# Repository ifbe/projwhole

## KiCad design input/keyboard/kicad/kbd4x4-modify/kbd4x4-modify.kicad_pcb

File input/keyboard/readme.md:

# ESP32-S3 三模键盘

ESP32-S3 机械键盘：**USB HID / 蓝牙 BLE / WiFi(UDP)** 三路同时输出，每键 WS2812B 灯效，
8×18 与 4×4(arrow) 两种矩阵在编译期切换，板载网页可以改键值、改灯效、看日志、重启/进下载模式。

## 目录

| 路径 | 内容 |
|---|---|
| `code/keyled/` | Arduino 固件（`keyled.ino` + 各模块） |
| `kicad/` | PCB 工程（kbd2x2 / kbd4x4 / kbd5x5 / esp32s3-wroom1 底板） |
| `scad/` | 外壳与键帽（OpenSCAD，以及导出的 stl / 3mf） |

## 其他文档

- [`arduino.md`](arduino.md) —— 开发环境、编译参数、烧录方式、网页入口
- [`gotcha.md`](gotcha.md) —— 踩过的坑（NimBLE / USB CDC / 下载模式 / EEPROM / 中断…）
- [`esp32s3.md`](esp32s3.md) —— ESP32-S3 引脚用途（8x18 + board v2），含未使用脚清单
- [`todo.md`](todo.md) —— 待办与已知问题

## 相关链接

- Arduino ESP32 core：<https://github.com/espressif/arduino-esp32>
- ESP32-S3 产品页/文档：<https://www.espressif.com/en/products/socs/esp32-s3>
- ESP32-BLE-Keyboard：<https://github.com/T-vK/ESP32-BLE-Keyboard>
- Adafruit NeoPixel：<https://github.com/adafruit/Adafruit_NeoPixel>
- esptool：<https://github.com/espressif/esptool>

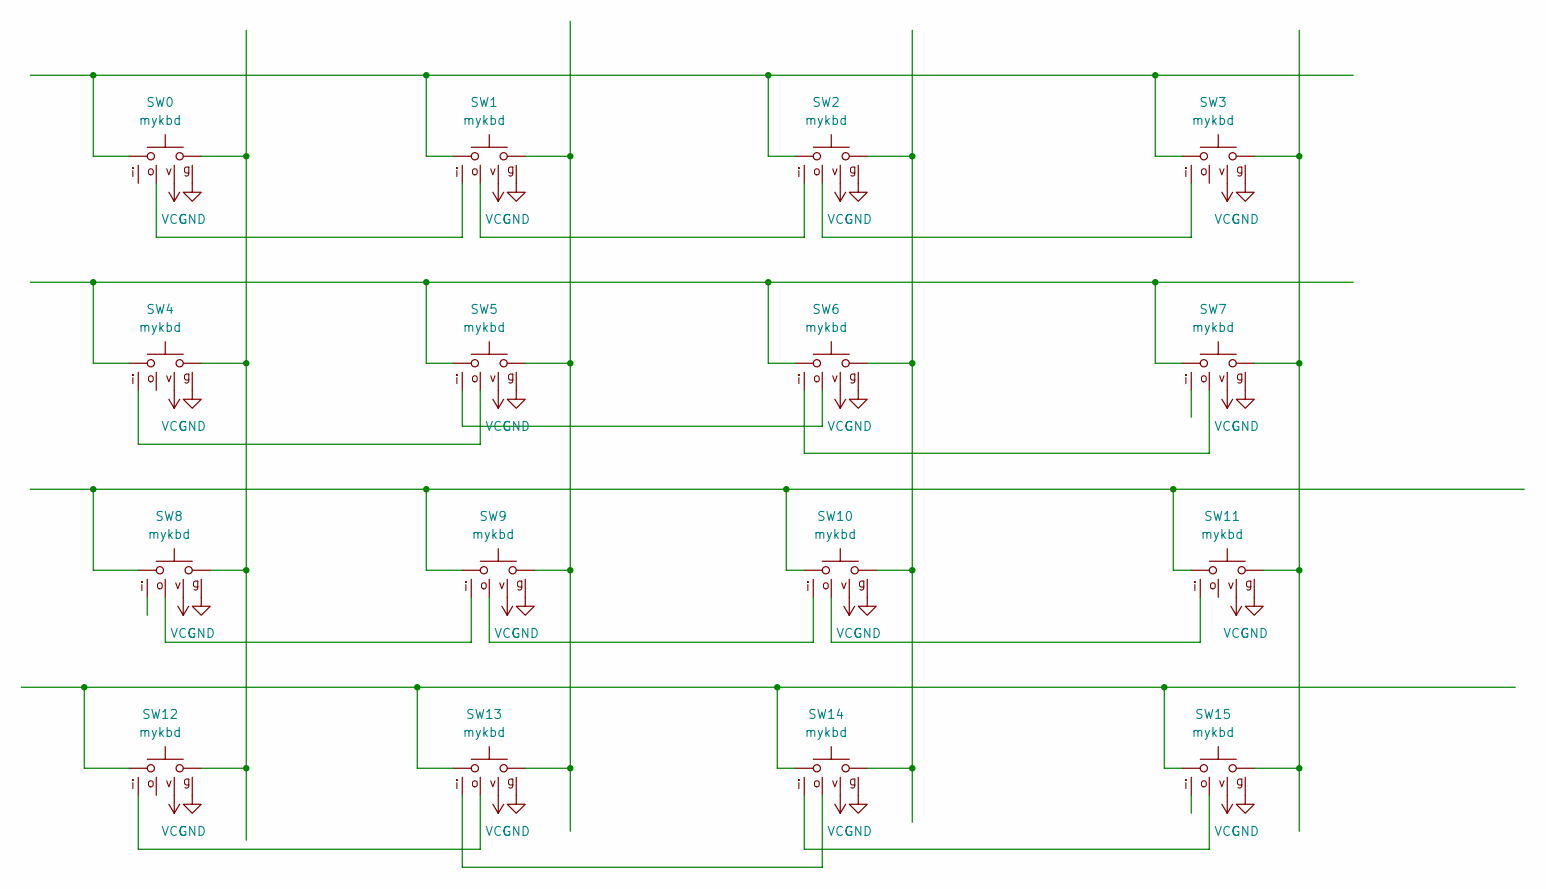
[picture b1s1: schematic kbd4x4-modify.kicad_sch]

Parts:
SW0, SW1, SW2, SW3, SW8, SW9, SW10, SW11: mykbd; seat_ltor
SW4, SW5, SW6, SW7, SW12, SW13, SW14, SW15: mykbd; seat_rtol

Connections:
GND: SW0.6, SW1.6, SW2.6, SW3.6, SW4.6, SW5.6, SW6.6, SW7.6, SW8.6, SW9.6, SW10.6, SW11.6, SW12.6, SW13.6, SW14.6, SW15.6
unnamed: SW0.1, SW1.1, SW2.1, SW3.1
unnamed: SW0.2, SW4.2, SW8.2, SW12.2
unnamed: SW0.4, SW1.3
unnamed: SW1.2, SW5.2, SW9.2, SW13.2
unnamed: SW1.4, SW2.3
unnamed: SW2.4, SW3.3
unnamed: SW4.1, SW5.1, SW6.1, SW7.1
unnamed: SW4.3, SW5.4
unnamed: SW5.3, SW6.4
unnamed: SW6.3, SW7.4
unnamed: SW8.4, SW9.3
unnamed: SW8.1, SW9.1, SW10.1, SW11.1
unnamed: SW2.2, SW6.2, SW10.2, SW14.2
unnamed: SW9.4, SW10.3
unnamed: SW10.4, SW11.3
unnamed: SW3.2, SW7.2, SW11.2, SW15.2
unnamed: SW12.1, SW13.1, SW14.1, SW15.1
unnamed: SW12.3, SW13.4
unnamed: SW13.3, SW14.4
unnamed: SW14.3, SW15.4
VCC: SW0.5, SW1.5, SW2.5, SW3.5, SW4.5, SW5.5, SW6.5, SW7.5, SW8.5, SW9.5, SW10.5, SW11.5, SW12.5, SW13.5, SW14.5, SW15.5

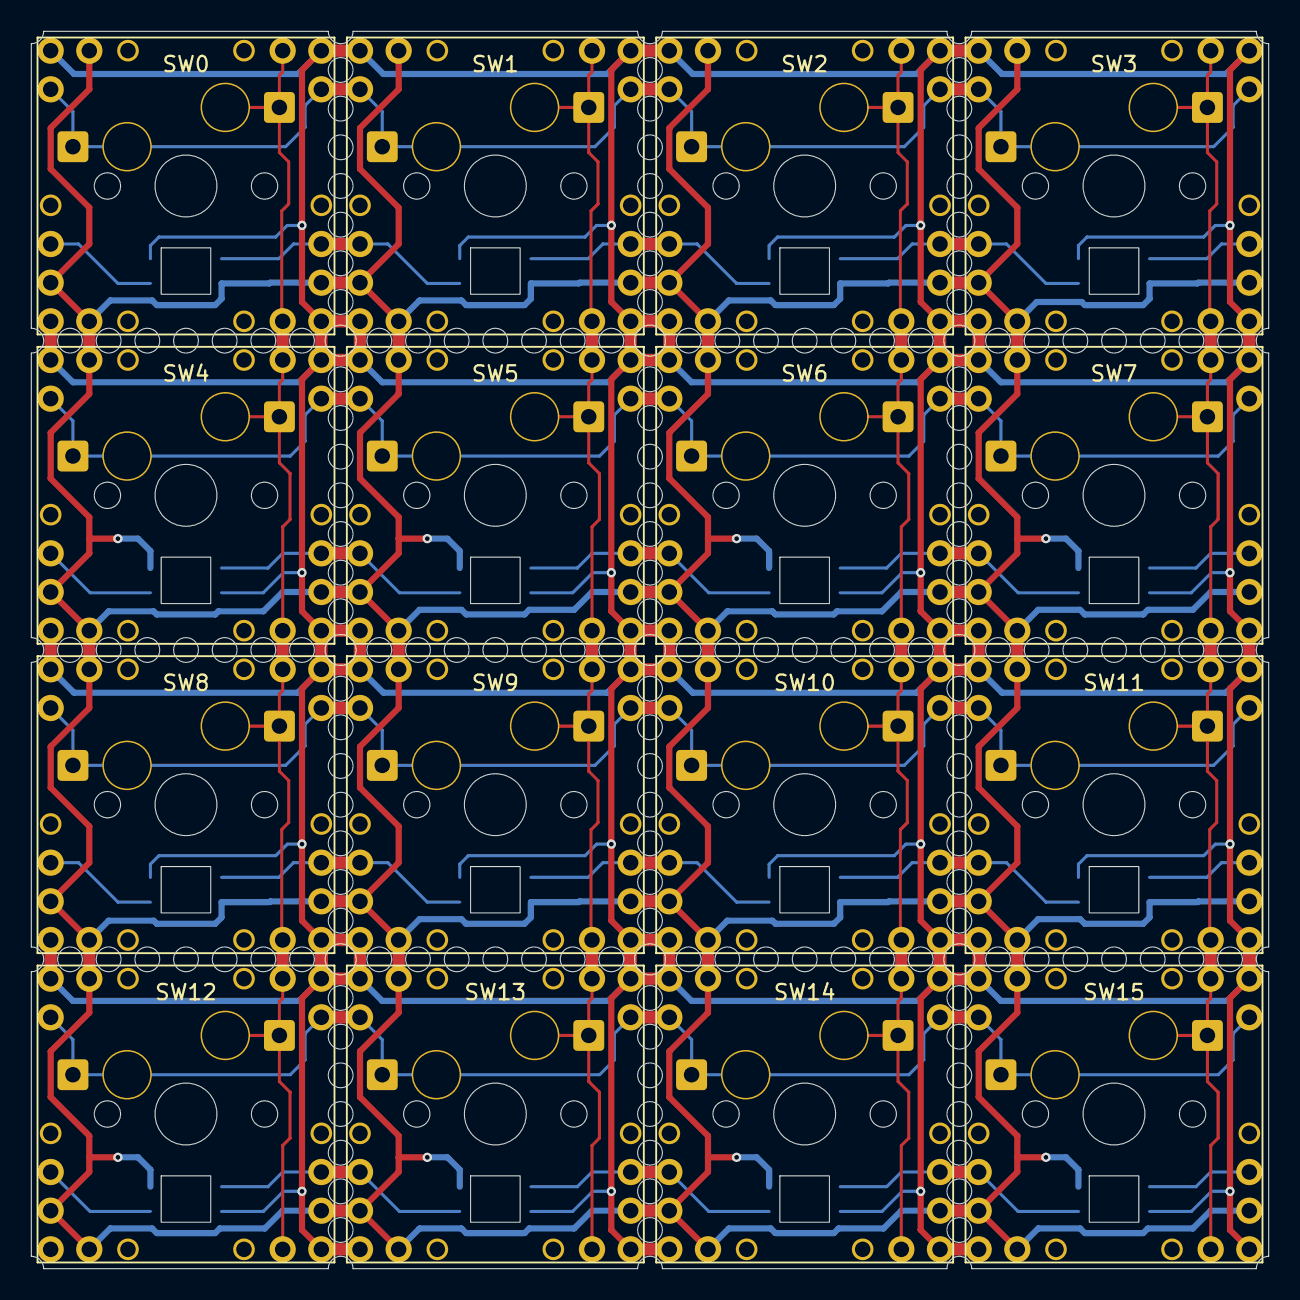
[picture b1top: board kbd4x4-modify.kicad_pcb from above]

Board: 2 copper layers, 80.0 x 80.0 mm, 16 parts (0 on the bottom side), 22 nets.

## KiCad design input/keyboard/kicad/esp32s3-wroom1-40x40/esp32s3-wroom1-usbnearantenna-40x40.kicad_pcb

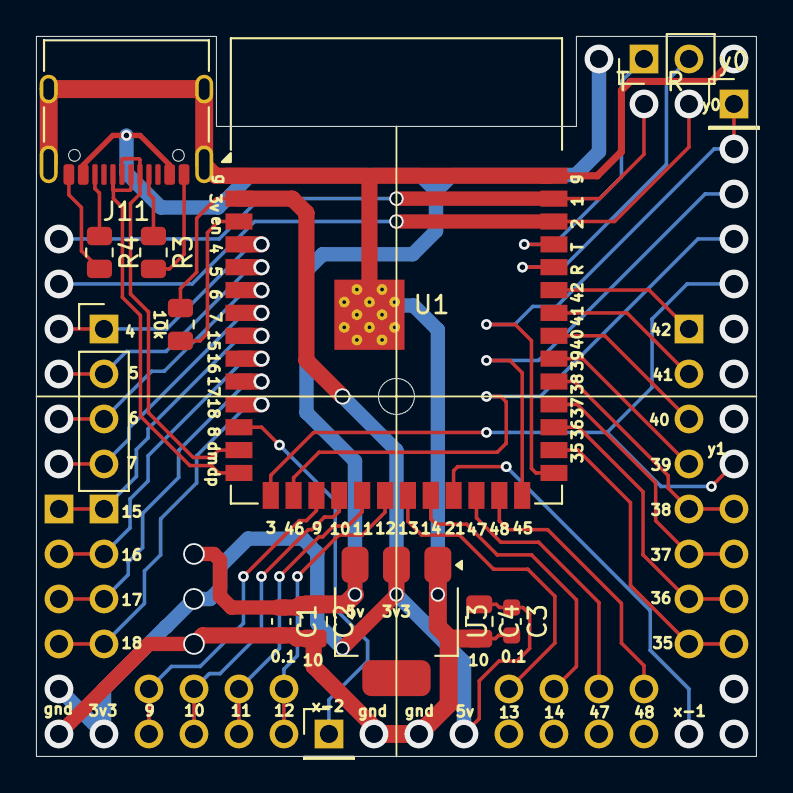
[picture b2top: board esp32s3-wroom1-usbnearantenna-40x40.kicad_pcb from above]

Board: 2 copper layers, 40.0 x 40.0 mm, 14 parts (0 on the bottom side), 16 nets.

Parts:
C1, C3: 0.1uf; C_0603_1608Metric
C2, C4: 10uf; C_0805_2012Metric
J10: Conn_01x01_Pin; PinHeader_1x01_P2.54mm_Vertical
J11: USB_C_Receptacle_USB2.0_16P; USB_C_Receptacle_XKB_U262-16XN-4BVC11
J12: Conn_01x02_Pin; PinHeader_1x02_P2.54mm_Vertical
J14: Conn_01x04_Pin; PinHeader_1x04_P2.54mm_Vertical
R1: R; R_0805_2012Metric
R3, R4: 5.1k; R_0805_2012Metric
U1: ESP32-S3-WROOM-1
U3: TLV1117-33; SOT-223
y0: Conn_01x01_Pin; PinHeader_1x01_P2.54mm_Vertical

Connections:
+3V3: C3.1, C4.1, R1.1, U1.2 (3V3), U3.2 (VO)
+5V: C1.1, C2.1, J11.A4 (VBUS), J11.A9 (VBUS), J11.B4 (VBUS), J11.B9 (VBUS), U3.3 (VI)
GND: C1.2, C2.2, C3.2, C4.2, J11.A1 (GND), J11.A12 (GND), J11.B1 (GND), J11.B12 (GND), J11.SH (SHIELD), R3.2, R4.2, U1.1 (GND), U1.40 (GND), U1.41 (GND), U3.1 (GND)
unnamed: J11.A5 (CC1), R3.1
unnamed: J11.B5 (CC2), R4.1
unnamed: R1.2, U1.3 (EN)
d+: J11.A6 (D+), J11.B6 (D+), U1.14 (USB_D+)
d-: J11.A7 (D-), J11.B7 (D-), U1.13 (USB_D-)
g0: U1.27 (IO0), y0.1
g4: J14.1, U1.4 (IO4)
g5: J14.2, U1.5 (IO5)
g6: J14.3, U1.6 (IO6)
g7: J14.4, U1.7 (IO7)
rx: J12.2, U1.36 (RXD0)
tx: J12.1, U1.37 (TXD0)
xl2: J10.1, U1.12 (IO8)

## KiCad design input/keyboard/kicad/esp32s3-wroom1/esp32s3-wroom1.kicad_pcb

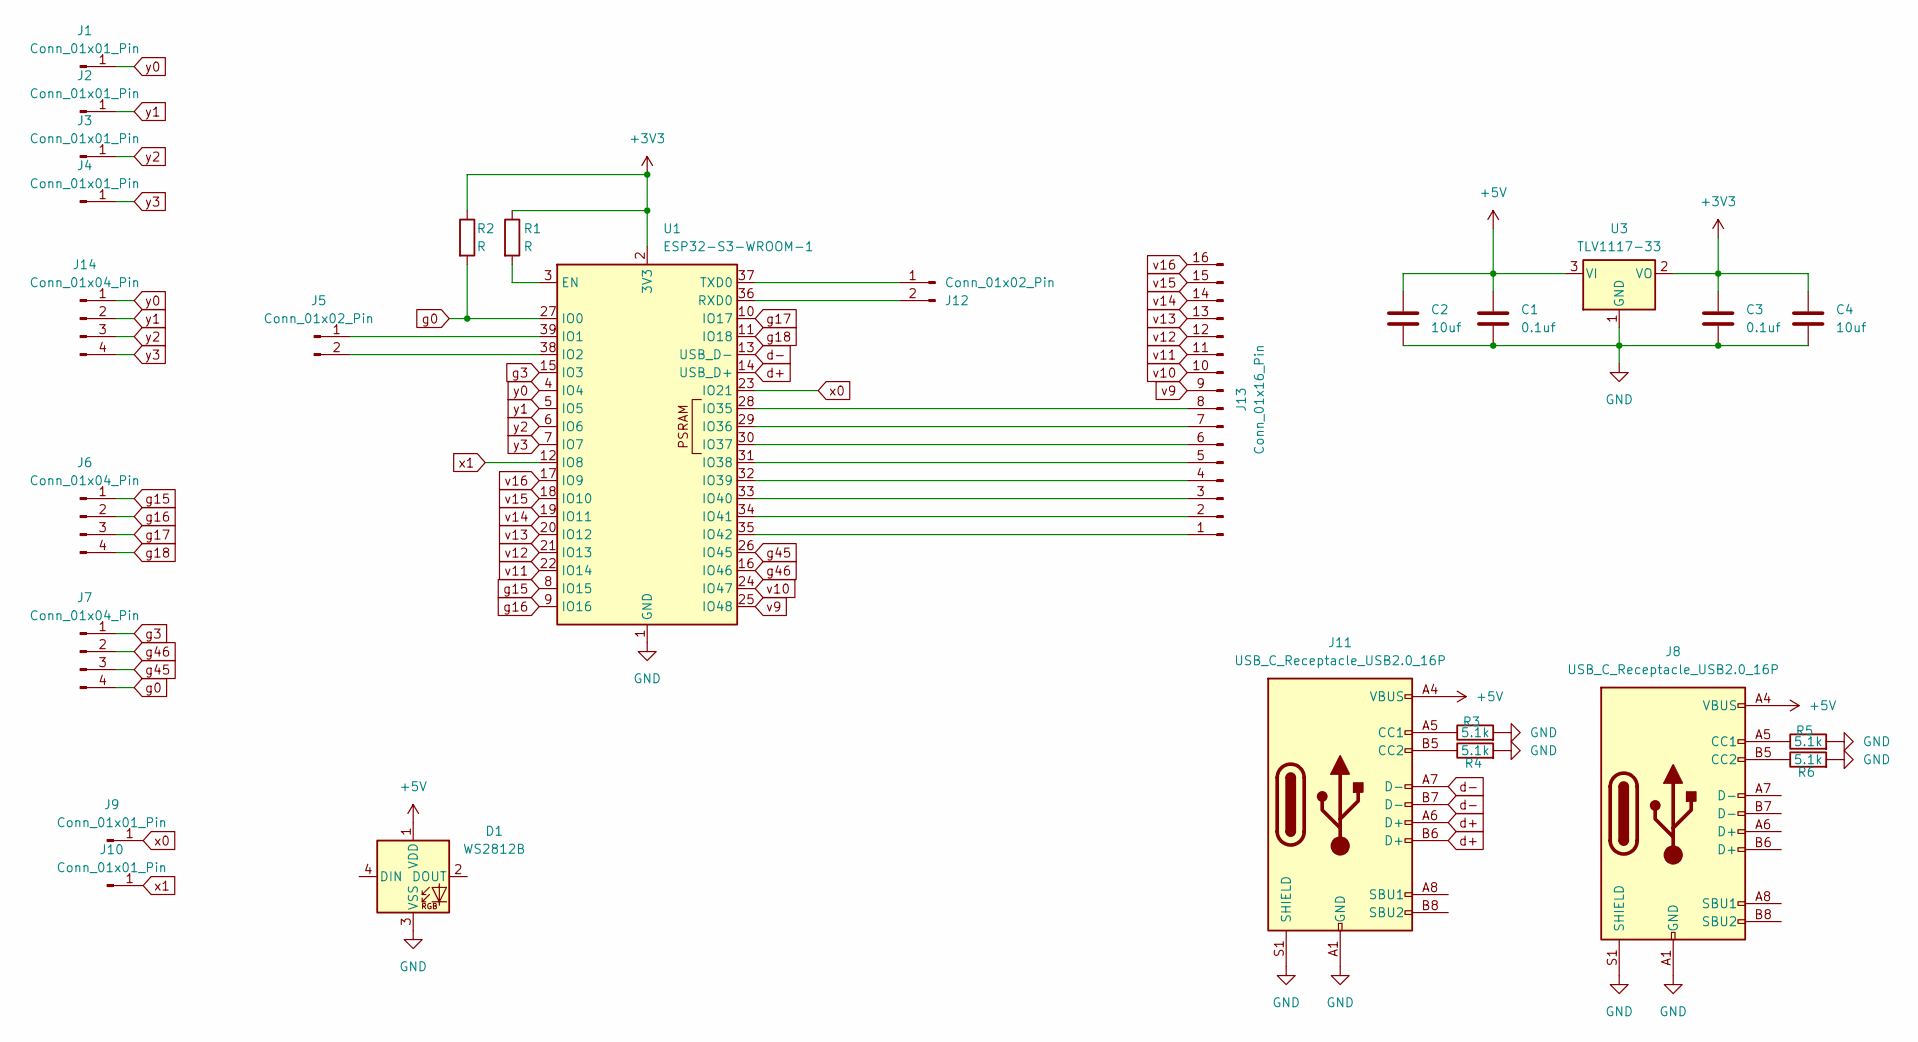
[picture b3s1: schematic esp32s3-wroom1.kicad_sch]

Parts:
C1, C3: 0.1uf; C_0603_1608Metric
C2, C4: 10uf; C_0805_2012Metric
D1: WS2812B; ws2812_3228back
J1, J2, J3, J4, J9, J10: Conn_01x01_Pin; PinHeader_1x01_P2.54mm_Vertical
J5, J12: Conn_01x02_Pin; PinHeader_1x02_P2.54mm_Vertical
J6, J7, J14: Conn_01x04_Pin; PinHeader_1x04_P2.54mm_Vertical
J8, J11: USB_C_Receptacle_USB2.0_16P; USB_C_Receptacle_XKB_U262-16XN-4BVC11
J13: Conn_01x16_Pin; PinHeader_1x16_P2.54mm_Vertical
R1, R2: R; R_0805_2012Metric
R3, R4, R5, R6: 5.1k; R_0805_2012Metric
U1: ESP32-S3-WROOM-1
U3: TLV1117-33; SOT-223

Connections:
+3V3: C3.1, C4.1, R1.1, R2.1, U1.2 (3V3), U3.2 (VO)
+5V: C1.1, C2.1, D1.1 (VDD), J8.A4 (VBUS), J8.A9 (VBUS), J8.B4 (VBUS), J8.B9 (VBUS), J11.A4 (VBUS), J11.A9 (VBUS), J11.B4 (VBUS), J11.B9 (VBUS), U3.3 (VI)
GND: C1.2, C2.2, C3.2, C4.2, D1.3 (VSS), J8.A1 (GND), J8.A12 (GND), J8.B1 (GND), J8.B12 (GND), J8.S1 (SHIELD), J11.A1 (GND), J11.A12 (GND), J11.B1 (GND), J11.B12 (GND), J11.S1 (SHIELD), R3.2, R4.2, R5.2, R6.2, U1.1 (GND), U1.40 (GND), U1.41 (GND), U3.1 (GND)
unnamed: J5.1, U1.39 (IO1)
unnamed: J5.2, U1.38 (IO2)
unnamed: J8.A5 (CC1), R5.1
unnamed: J8.B5 (CC2), R6.1
unnamed: J11.A5 (CC1), R3.1
unnamed: J11.B5 (CC2), R4.1
unnamed: J12.1, U1.37 (TXD0)
unnamed: J12.2, U1.36 (RXD0)
unnamed: J13.1, U1.35 (IO42)
unnamed: J13.2, U1.34 (IO41)
unnamed: J13.3, U1.33 (IO40)
unnamed: J13.4, U1.32 (IO39)
unnamed: J13.5, U1.31 (IO38)
unnamed: J13.6, U1.30 (IO37)
unnamed: J13.7, U1.29 (IO36)
unnamed: J13.8, U1.28 (IO35)
unnamed: R1.2, U1.3 (EN)
d+: J11.A6 (D+), J11.B6 (D+), U1.14 (USB_D+)
d-: J11.A7 (D-), J11.B7 (D-), U1.13 (USB_D-)
g0: J7.4, R2.2, U1.27 (IO0)
g3: J7.1, U1.15 (IO3)
g15: J6.1, U1.8 (IO15)
g16: J6.2, U1.9 (IO16)
g17: J6.3, U1.10 (IO17)
g18: J6.4, U1.11 (IO18)
g45: J7.3, U1.26 (IO45)
g46: J7.2, U1.16 (IO46)
v9: J13.9, U1.25 (IO48)
v10: J13.10, U1.24 (IO47)
v11: J13.11, U1.22 (IO14)
v12: J13.12, U1.21 (IO13)
v13: J13.13, U1.20 (IO12)
v14: J13.14, U1.19 (IO11)
v15: J13.15, U1.18 (IO10)
v16: J13.16, U1.17 (IO9)
x0: J9.1, U1.23 (IO21); also elsewhere on the board
x1: J10.1, U1.12 (IO8)
y0: J1.1, J14.1, U1.4 (IO4)
y1: J2.1, J14.2, U1.5 (IO5)
y2: J3.1, J14.3, U1.6 (IO6)
y3: J4.1, J14.4, U1.7 (IO7)

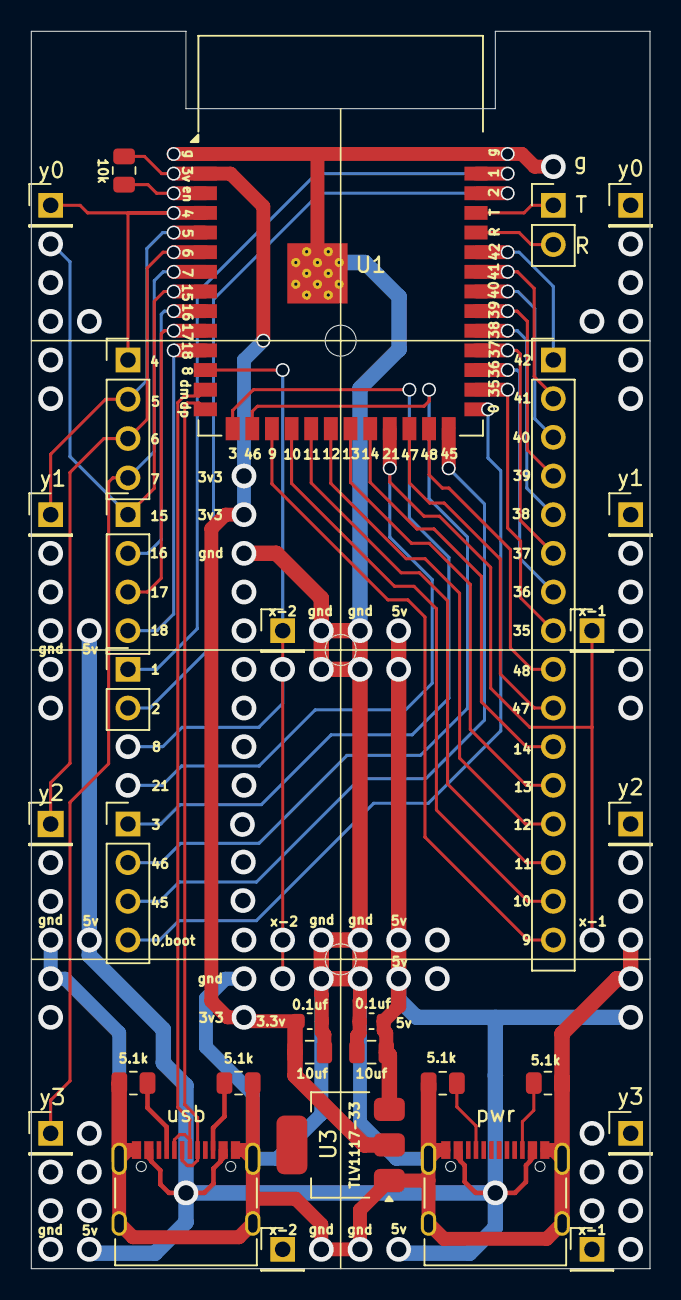
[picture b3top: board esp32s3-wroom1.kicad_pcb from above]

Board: 2 copper layers, 40.0 x 80.0 mm, 31 parts (0 on the bottom side), 44 nets.

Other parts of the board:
J9#2: Conn_01x01_Pin; PinHeader_1x01_P2.54mm_Vertical
x-2: Conn_01x01_Pin; PinHeader_1x01_P2.54mm_Vertical
y0, y1, y2, y3: Conn_01x01_Pin; PinHeader_1x01_P2.54mm_Vertical

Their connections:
x0: J9#2.1; also elsewhere on the board

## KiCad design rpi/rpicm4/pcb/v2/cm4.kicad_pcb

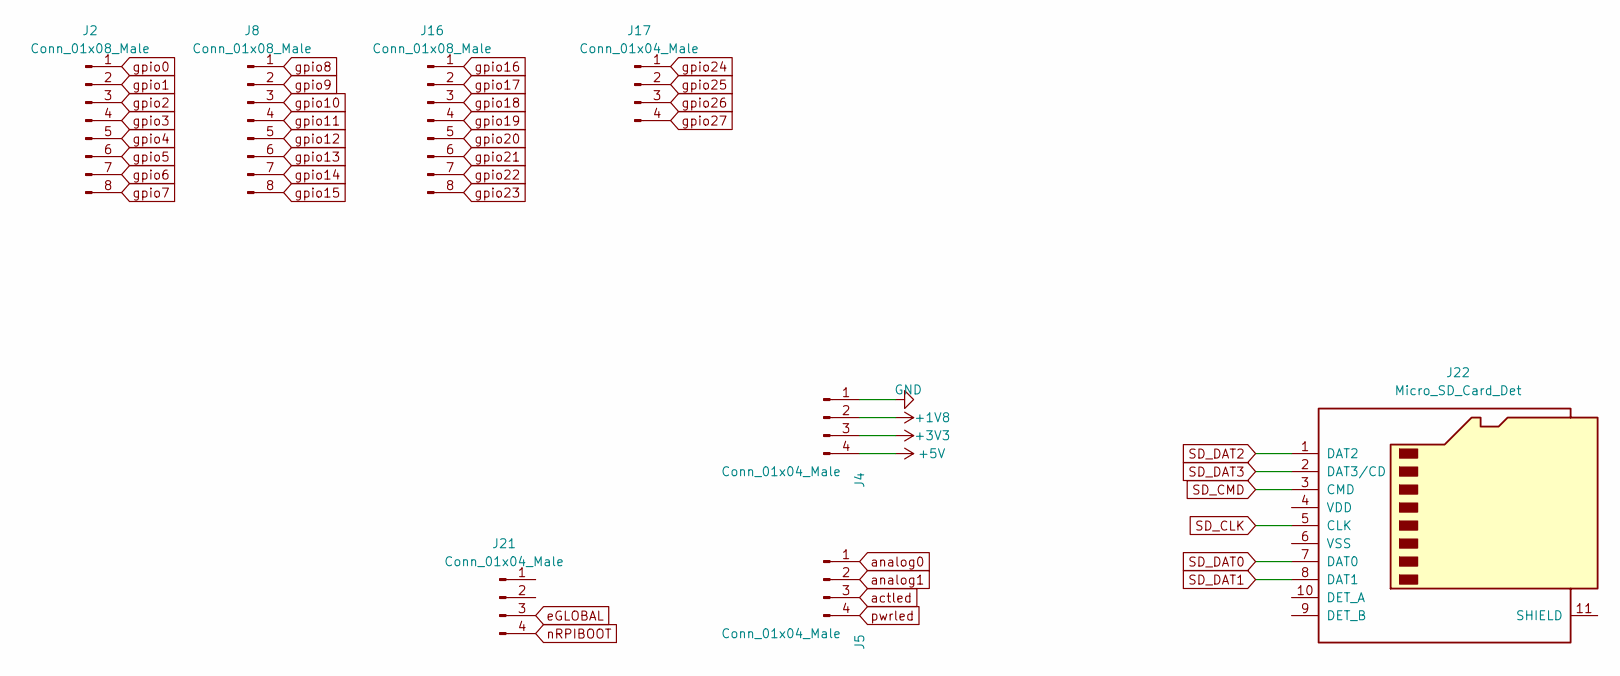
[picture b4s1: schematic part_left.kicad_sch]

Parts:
J2, J8, J16: Conn_01x08_Male; PinHeader_1x08_P2.54mm_Vertical
J4, J5, J17, J21: Conn_01x04_Male; PinHeader_1x04_P2.54mm_Vertical
J22: Micro_SD_Card_Det; SDCARD_MOLEX_503398-1892

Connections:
+1V8: J4.2; also elsewhere on the board
+3V3: J4.3; also elsewhere on the board
+5V: J4.4; also elsewhere on the board
GND: J4.1; also elsewhere on the board
SD_CLK: J22.5 (CLK); also elsewhere on the board
SD_CMD: J22.3 (CMD); also elsewhere on the board
SD_DAT0: J22.7 (DAT0); also elsewhere on the board
SD_DAT1: J22.8 (DAT1); also elsewhere on the board
SD_DAT2: J22.1 (DAT2); also elsewhere on the board
SD_DAT3: J22.2 (DAT3/CD); also elsewhere on the board
actled: J5.3; also elsewhere on the board
analog0: J5.1; also elsewhere on the board
analog1: J5.2; also elsewhere on the board
eGLOBAL: J21.3; also elsewhere on the board
gpio0: J2.1; also elsewhere on the board
gpio1: J2.2; also elsewhere on the board
gpio2: J2.3; also elsewhere on the board
gpio3: J2.4; also elsewhere on the board
gpio4: J2.5; also elsewhere on the board
gpio5: J2.6; also elsewhere on the board
gpio6: J2.7; also elsewhere on the board
gpio7: J2.8; also elsewhere on the board
gpio8: J8.1; also elsewhere on the board
gpio9: J8.2; also elsewhere on the board
gpio10: J8.3; also elsewhere on the board
gpio11: J8.4; also elsewhere on the board
gpio12: J8.5; also elsewhere on the board
gpio13: J8.6; also elsewhere on the board
gpio14: J8.7; also elsewhere on the board
gpio15: J8.8; also elsewhere on the board
gpio16: J16.1; also elsewhere on the board
gpio17: J16.2; also elsewhere on the board
gpio18: J16.3; also elsewhere on the board
gpio19: J16.4; also elsewhere on the board
gpio20: J16.5; also elsewhere on the board
gpio21: J16.6; also elsewhere on the board
gpio22: J16.7; also elsewhere on the board
gpio23: J16.8; also elsewhere on the board
gpio24: J17.1; also elsewhere on the board
gpio25: J17.2; also elsewhere on the board
gpio26: J17.3; also elsewhere on the board
gpio27: J17.4; also elsewhere on the board
nRPIBOOT: J21.4; also elsewhere on the board
pwrled: J5.4; also elsewhere on the board

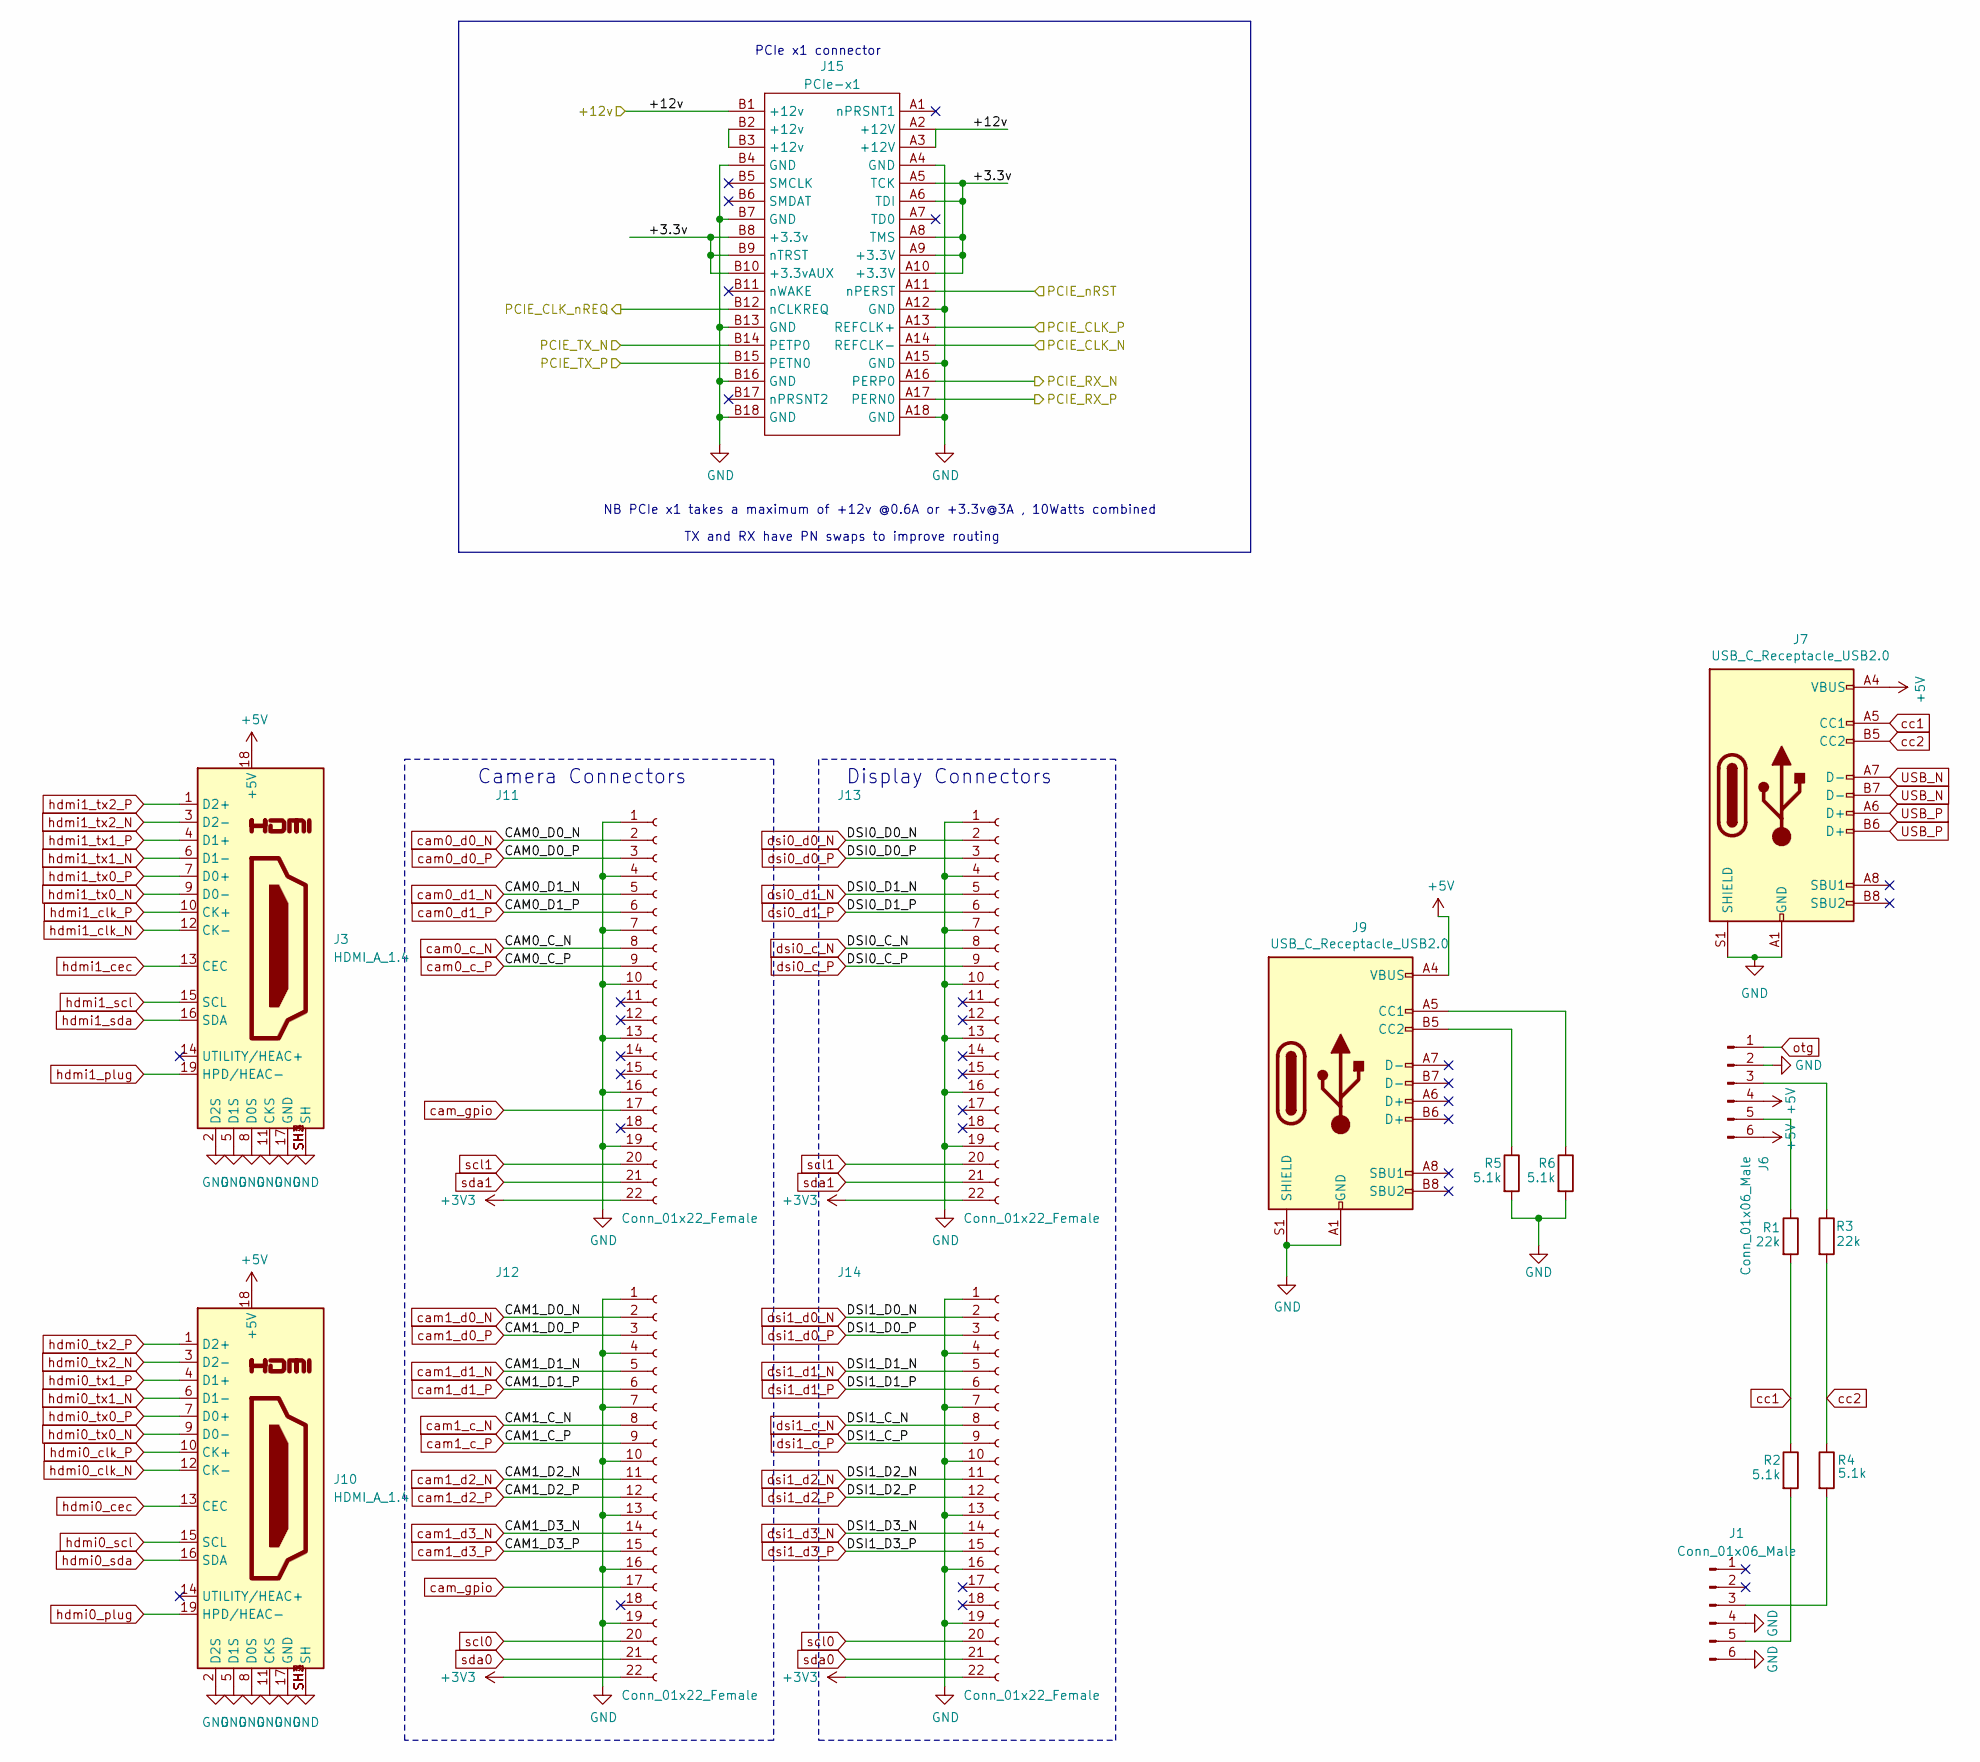
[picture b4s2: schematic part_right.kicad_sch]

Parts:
J1, J6: Conn_01x06_Male; PinHeader_1x06_P2.54mm_Vertical
J3, J10: HDMI_A_1.4; HDMI_Micro-D_Molex_46765-1x01
J7, J9: USB_C_Receptacle_USB2.0; USB_C_Receptacle_XKB_U262-16XN-4BVC11
J11, J12, J13, J14: Conn_01x22_Female; Hirose_FH12-22S-0.5SH_1x22-1MP_P0.50mm_Horizontal; Part Description 22 Position FFC, FPC Connector Contacts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
J15: PCIe-x1; PCIex1-36
R1, R3: 22k; R_Axial_DIN0207_L6.3mm_D2.5mm_P10.16mm_Horizontal
R2, R4, R5, R6: 5.1k; R_Axial_DIN0207_L6.3mm_D2.5mm_P10.16mm_Horizontal

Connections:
+3V3: J11.22, J12.22, J13.22, J14.22; also elsewhere on the board
+5V: J3.18 (+5V), J6.4, J6.6, J7.A4 (VBUS), J7.A9 (VBUS), J7.B4 (VBUS), J7.B9 (VBUS), J9.A4 (VBUS), J9.A9 (VBUS), J9.B4 (VBUS), J9.B9 (VBUS), J10.18 (+5V); also elsewhere on the board
GND: J1.4, J1.6, J3.2 (D2S), J3.5 (D1S), J3.8 (D0S), J3.11 (CKS), J3.17 (GND), J3.SH1 (SH), J3.SH2 (SH), J3.SH3 (SH), J3.SH4 (SH), J6.2, J7.A1 (GND), J7.A12 (GND), J7.B1 (GND), J7.B12 (GND), J7.S1 (SHIELD), J9.A1 (GND), J9.A12 (GND), J9.B1 (GND), J9.B12 (GND), J9.S1 (SHIELD), J10.2 (D2S), J10.5 (D1S), J10.8 (D0S), J10.11 (CKS), J10.17 (GND), J10.SH1 (SH), J10.SH2 (SH), J10.SH3 (SH), J10.SH4 (SH), J11.1, J11.4, J11.7, J11.10, J11.13, J11.16, J11.19, J12.1, J12.4, J12.7, J12.10, J12.13, J12.16, J12.19, J13.1, J13.4, J13.7, J13.10, J13.13, J13.16, J13.19, J14.1, J14.4, J14.7, J14.10, J14.13, J14.16, J14.19, J15.A4 (GND), J15.A12 (GND), J15.A15 (GND), J15.A18 (GND), J15.B4 (GND), J15.B7 (GND), J15.B13 (GND), J15.B16 (GND), J15.B18 (GND), R5.2, R6.2; also elsewhere on the board
unnamed: J1.3, R4.2
unnamed: J1.5, R2.2
unnamed: J6.3, R3.1
unnamed: J6.5, R1.1
unnamed: J9.A5 (CC1), R6.1
unnamed: J9.B5 (CC2), R5.1
unnamed: J15.A2 (+12V), J15.A3 (+12V), J15.B1 (+12v)
unnamed: J15.A5 (TCK), J15.A6 (TDI), J15.A8 (TMS), J15.A9 (+3.3V), J15.A10 (+3.3V), J15.B8 (+3.3v), J15.B9 (nTRST), J15.B10 (+3.3vAUX)
unnamed: J15.B2 (+12v), J15.B3 (+12v)
USB_N: J7.A7 (D-), J7.B7 (D-); also elsewhere on the board
USB_P: J7.A6 (D+), J7.B6 (D+); also elsewhere on the board
cam0_c_N: J11.8; also elsewhere on the board
cam0_c_P: J11.9; also elsewhere on the board
cam0_d0_N: J11.2; also elsewhere on the board
cam0_d0_P: J11.3; also elsewhere on the board
cam0_d1_N: J11.5; also elsewhere on the board
cam0_d1_P: J11.6; also elsewhere on the board
cam1_c_N: J12.8; also elsewhere on the board
cam1_c_P: J12.9; also elsewhere on the board
cam1_d0_N: J12.2
cam1_d0_P: J12.3
cam1_d1_N: J12.5; also elsewhere on the board
cam1_d1_P: J12.6; also elsewhere on the board
cam1_d2_N: J12.11; also elsewhere on the board
cam1_d2_P: J12.12; also elsewhere on the board
cam1_d3_N: J12.14; also elsewhere on the board
cam1_d3_P: J12.15; also elsewhere on the board
cam_gpio: J11.17, J12.17; also elsewhere on the board
cc1: J7.A5 (CC1), R1.2, R2.1
cc2: J7.B5 (CC2), R3.2, R4.1
dsi0_c_N: J13.8; also elsewhere on the board
dsi0_c_P: J13.9; also elsewhere on the board
dsi0_d0_N: J13.2; also elsewhere on the board
dsi0_d0_P: J13.3; also elsewhere on the board
dsi0_d1_N: J13.5; also elsewhere on the board
dsi0_d1_P: J13.6; also elsewhere on the board
dsi1_c_N: J14.8; also elsewhere on the board
dsi1_c_P: J14.9; also elsewhere on the board
dsi1_d0_N: J14.2; also elsewhere on the board
dsi1_d0_P: J14.3; also elsewhere on the board
dsi1_d1_N: J14.5; also elsewhere on the board
dsi1_d1_P: J14.6; also elsewhere on the board
dsi1_d2_N: J14.11; also elsewhere on the board
dsi1_d2_P: J14.12; also elsewhere on the board
dsi1_d3_N: J14.14; also elsewhere on the board
dsi1_d3_P: J14.15; also elsewhere on the board
hdmi0_cec: J10.13 (CEC); also elsewhere on the board
hdmi0_clk_N: J10.12 (CK-); also elsewhere on the board
hdmi0_clk_P: J10.10 (CK+); also elsewhere on the board
hdmi0_plug: J10.19 (HPD/HEAC-); also elsewhere on the board
hdmi0_scl: J10.15 (SCL); also elsewhere on the board
hdmi0_sda: J10.16 (SDA); also elsewhere on the board
hdmi0_tx0_N: J10.9 (D0-); also elsewhere on the board
hdmi0_tx0_P: J10.7 (D0+); also elsewhere on the board
hdmi0_tx1_N: J10.6 (D1-); also elsewhere on the board
hdmi0_tx1_P: J10.4 (D1+); also elsewhere on the board
hdmi0_tx2_N: J10.3 (D2-); also elsewhere on the board
hdmi0_tx2_P: J10.1 (D2+); also elsewhere on the board
hdmi1_cec: J3.13 (CEC); also elsewhere on the board
hdmi1_clk_N: J3.12 (CK-); also elsewhere on the board
hdmi1_clk_P: J3.10 (CK+); also elsewhere on the board
hdmi1_plug: J3.19 (HPD/HEAC-); also elsewhere on the board
hdmi1_scl: J3.15 (SCL); also elsewhere on the board
hdmi1_sda: J3.16 (SDA); also elsewhere on the board
hdmi1_tx0_N: J3.9 (D0-); also elsewhere on the board
hdmi1_tx0_P: J3.7 (D0+); also elsewhere on the board
hdmi1_tx1_N: J3.6 (D1-); also elsewhere on the board
hdmi1_tx1_P: J3.4 (D1+); also elsewhere on the board
hdmi1_tx2_N: J3.3 (D2-); also elsewhere on the board
hdmi1_tx2_P: J3.1 (D2+); also elsewhere on the board
otg: J6.1; also elsewhere on the board
scl0: J12.20, J14.20; also elsewhere on the board
scl1: J11.20, J13.20
sda0: J12.21, J14.21; also elsewhere on the board
sda1: J11.21, J13.21

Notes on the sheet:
Camera Connectors
TX and RX have PN swaps to improve routing
NB PCIe x1 takes a maximum of +12v @0.6A or +3.3v@3A , 10Watts combined
PCIe x1 connector
Display Connectors
